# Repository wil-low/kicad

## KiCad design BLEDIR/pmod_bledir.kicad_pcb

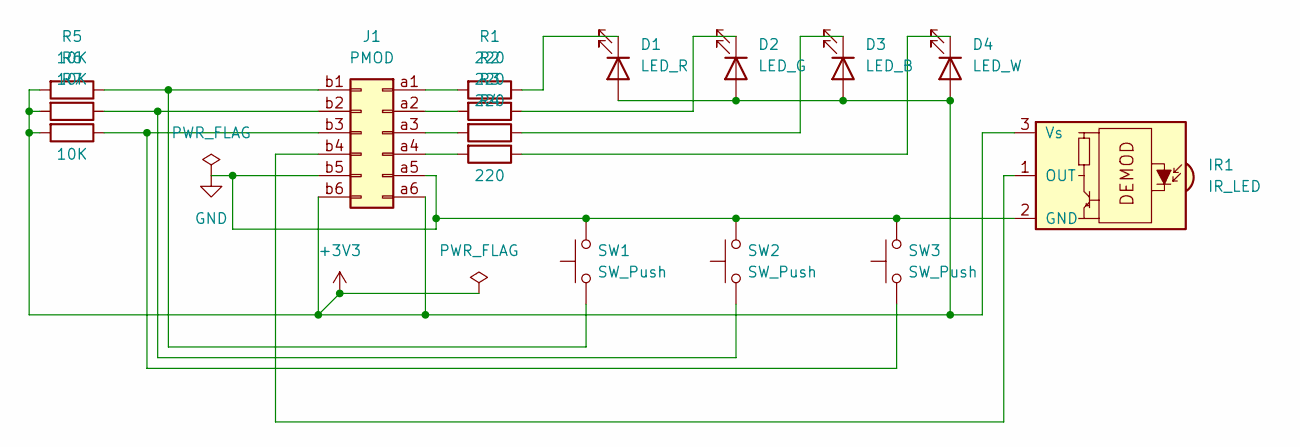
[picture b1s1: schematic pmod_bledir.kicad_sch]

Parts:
D1: LED_R; LED_D5.0mm
D2: LED_G; LED_D5.0mm
D3: LED_B; LED_D5.0mm
D4: LED_W; LED_D5.0mm
IR1: IR_LED; Vishay_MOLD-3Pin
J1: PMOD; PMOD_2x06
R1, R2, R3, R4: 220; R_Axial_DIN0204_L3.6mm_D1.6mm_P7.62mm_Horizontal
R5, R6, R7: 10K; R_Axial_DIN0204_L3.6mm_D1.6mm_P7.62mm_Horizontal
SW1, SW2, SW3: SW_Push; SW_PUSH_6mm

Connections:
+3V3: D1.2 (A), D2.2 (A), D3.2 (A), D4.2 (A), IR1.3 (Vs), J1.a6, J1.b6, R5.2, R6.2, R7.2
GND: IR1.2 (GND), J1.a5, J1.b5, SW1.2, SW2.2, SW3.2
unnamed: D1.1 (K), R1.1
unnamed: D2.1 (K), R2.1
unnamed: D3.1 (K), R3.1
unnamed: D4.1 (K), R4.1
unnamed: IR1.1 (OUT), J1.b4
unnamed: J1.a1, R1.2
unnamed: J1.a2, R2.2
unnamed: J1.a3, R3.2
unnamed: J1.a4, R4.2
unnamed: J1.b3, R7.1, SW3.1
unnamed: J1.b1, R5.1, SW1.1
unnamed: J1.b2, R6.1, SW2.1

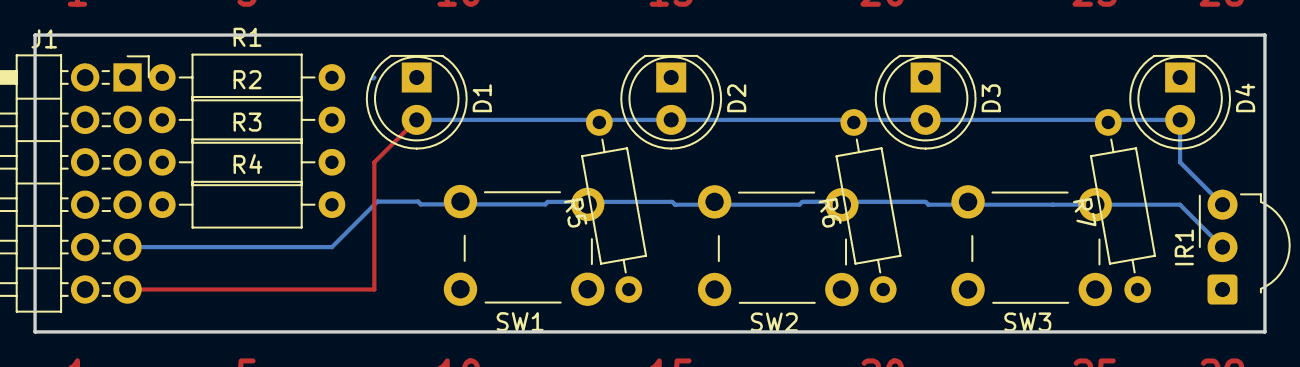
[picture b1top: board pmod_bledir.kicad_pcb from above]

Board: 2 copper layers, 73.7 x 17.8 mm, 16 parts (0 on the bottom side), 14 nets.

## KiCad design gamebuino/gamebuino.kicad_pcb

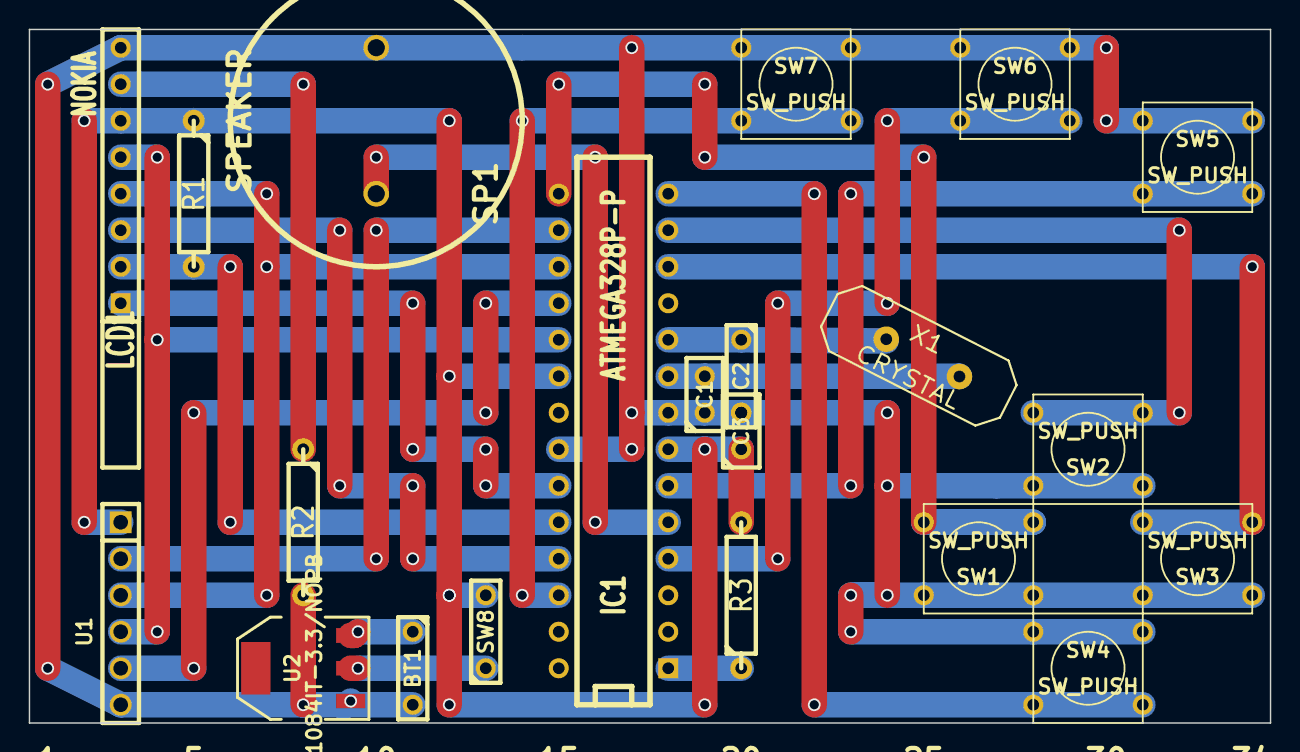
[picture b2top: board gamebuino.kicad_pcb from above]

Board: 2 copper layers, 86.4 x 48.3 mm, 21 parts (0 on the bottom side), 23 nets.

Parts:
BT1: BATTERY; C2
C1: 22p; C1
C2: 22p; C2
C3: 10u; C1
IC1: ATMEGA328P-P; DIP-28__300
LCD1: NOKIA
R1, R3: 10K; R4
R2: 220; R4
SP1: SPEAKER; BUZZER
SW1, SW2, SW3, SW4, SW5, SW6, SW7: SW_PUSH; SW_PUSH_SMALL_1
SW8: SPST; C2
U1: SDCARD
U2: LM1084IT-3.3/NOPB; SOT223
X1: CRYSTAL; HC-18UV-rotated

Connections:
/BTN0: IC1.15, SW1.2
/BTN1: IC1.13, SW2.2
/BTN2: IC1.12, SW3.2
/BTN3: IC1.14, SW4.2
/BTNA: IC1.6, SW5.2
/BTNB: IC1.4, SW6.2
/BTNC: IC1.26, SW7.2
/MISO: IC1.18, U1.5
/MOSI: IC1.17, LCD1.4, U1.3
/RST: IC1.1, R3.1
/SCK: IC1.19, LCD1.5, U1.4
/SCR DC: IC1.25, LCD1.3
/SCR ENABLE: IC1.24, LCD1.2, R1.2
/SCR RST: IC1.23, LCD1.1
/SD ENABLE: IC1.16, U1.2
/SOUND: IC1.5, SP1.1
/VCC: C3.1, IC1.7, IC1.20, LCD1.6, R1.1, R3.2, SW8.2, U1.1
/VIN: BT1.1, U2.3
/VOUT: SW8.1, U2.2
/XTAL1: C1.2, IC1.9, X1.2
/XTAL2: C2.1, IC1.10, X1.1
GND: BT1.2, C1.1, C2.2, C3.2, IC1.8, IC1.22, LCD1.8, R2.2, SP1.2, SW1.1, SW2.1, SW3.1, SW4.1, SW5.1, SW6.1, SW7.1, U1.6, U2.1
unnamed: LCD1.7, R2.1

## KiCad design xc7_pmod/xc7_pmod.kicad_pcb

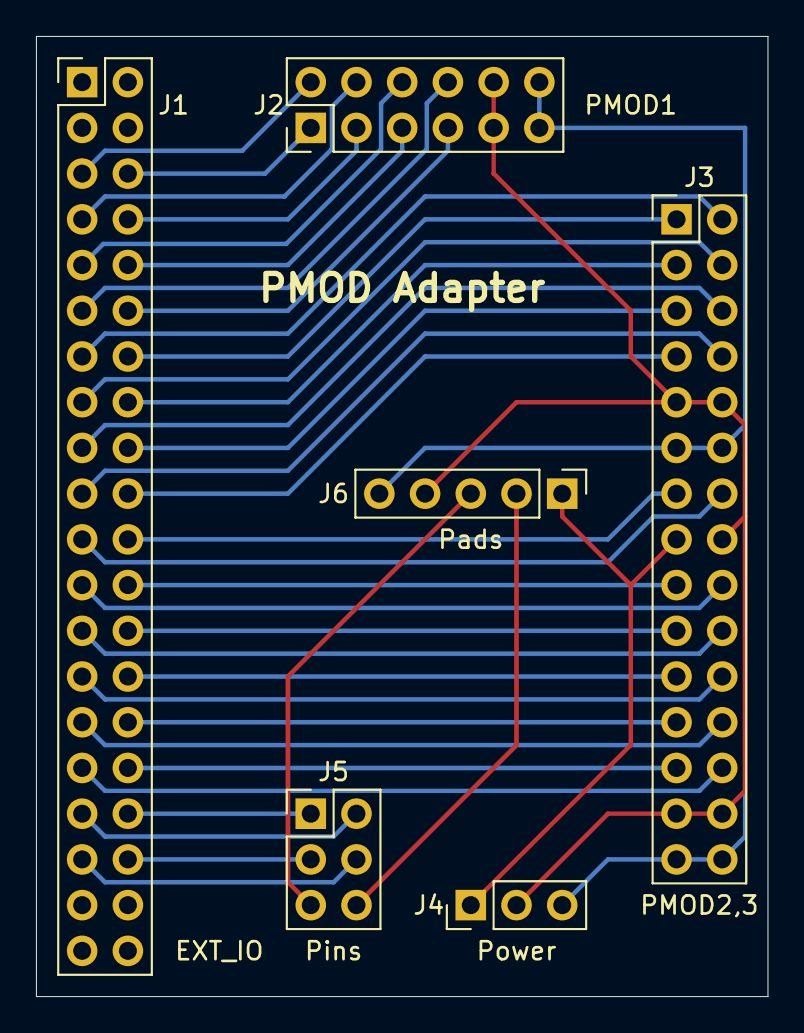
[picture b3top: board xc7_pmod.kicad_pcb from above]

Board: 2 copper layers, 40.6 x 53.3 mm, 6 parts (0 on the bottom side), 37 nets.

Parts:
J1: EXT_IO; PinHeader_2x20_P2.54mm_Vertical
J2: PMOD1; PinHeader_2x06_P2.54mm_Vertical
J3: PMOD2,3; PinHeader_2x15_P2.54mm_Vertical
J4: Power; PinHeader_1x03_P2.54mm_Vertical
J5: Pins; PinHeader_2x03_P2.54mm_Vertical
J6: Pads; PinHeader_1x05_P2.54mm_Vertical

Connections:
+3V3: J2.6, J2.7, J3.11, J3.12, J3.29, J3.30, J4.3, J6.5
+5V: J3.15, J4.1 (5V), J6.1
GND: J2.5, J2.8, J3.9, J3.10, J3.16, J3.27, J3.28, J4.2, J6.4
unnamed: J1.5, J2.12
unnamed: J1.6, J2.1
unnamed: J1.7, J2.11
unnamed: J1.8, J2.2
unnamed: J1.9, J2.10
unnamed: J1.10, J2.3
unnamed: J1.11, J2.9
unnamed: J1.12, J2.4
unnamed: J1.13, J3.2
unnamed: J1.14, J3.1
unnamed: J1.15, J3.4
unnamed: J1.16, J3.3
unnamed: J1.17, J3.6
unnamed: J1.18, J3.5
unnamed: J1.19, J3.8
unnamed: J1.20, J3.7
unnamed: J1.21, J3.14
unnamed: J1.22, J3.13
unnamed: J1.23, J3.18
unnamed: J1.24, J3.17
unnamed: J1.25, J3.20
unnamed: J1.26, J3.19
unnamed: J1.27, J3.22
unnamed: J1.28, J3.21
unnamed: J1.29, J3.24
unnamed: J1.30, J3.23
unnamed: J1.31, J3.26
unnamed: J1.32, J3.25
unnamed: J1.33, J5.2
unnamed: J1.34, J5.1
unnamed: J1.35, J5.4
unnamed: J1.36, J5.3
unnamed: J5.5, J6.3
unnamed: J5.6, J6.2

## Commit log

2023-04-29 Initial commit of BLEDIR, gamebuino, xc7_pmod
